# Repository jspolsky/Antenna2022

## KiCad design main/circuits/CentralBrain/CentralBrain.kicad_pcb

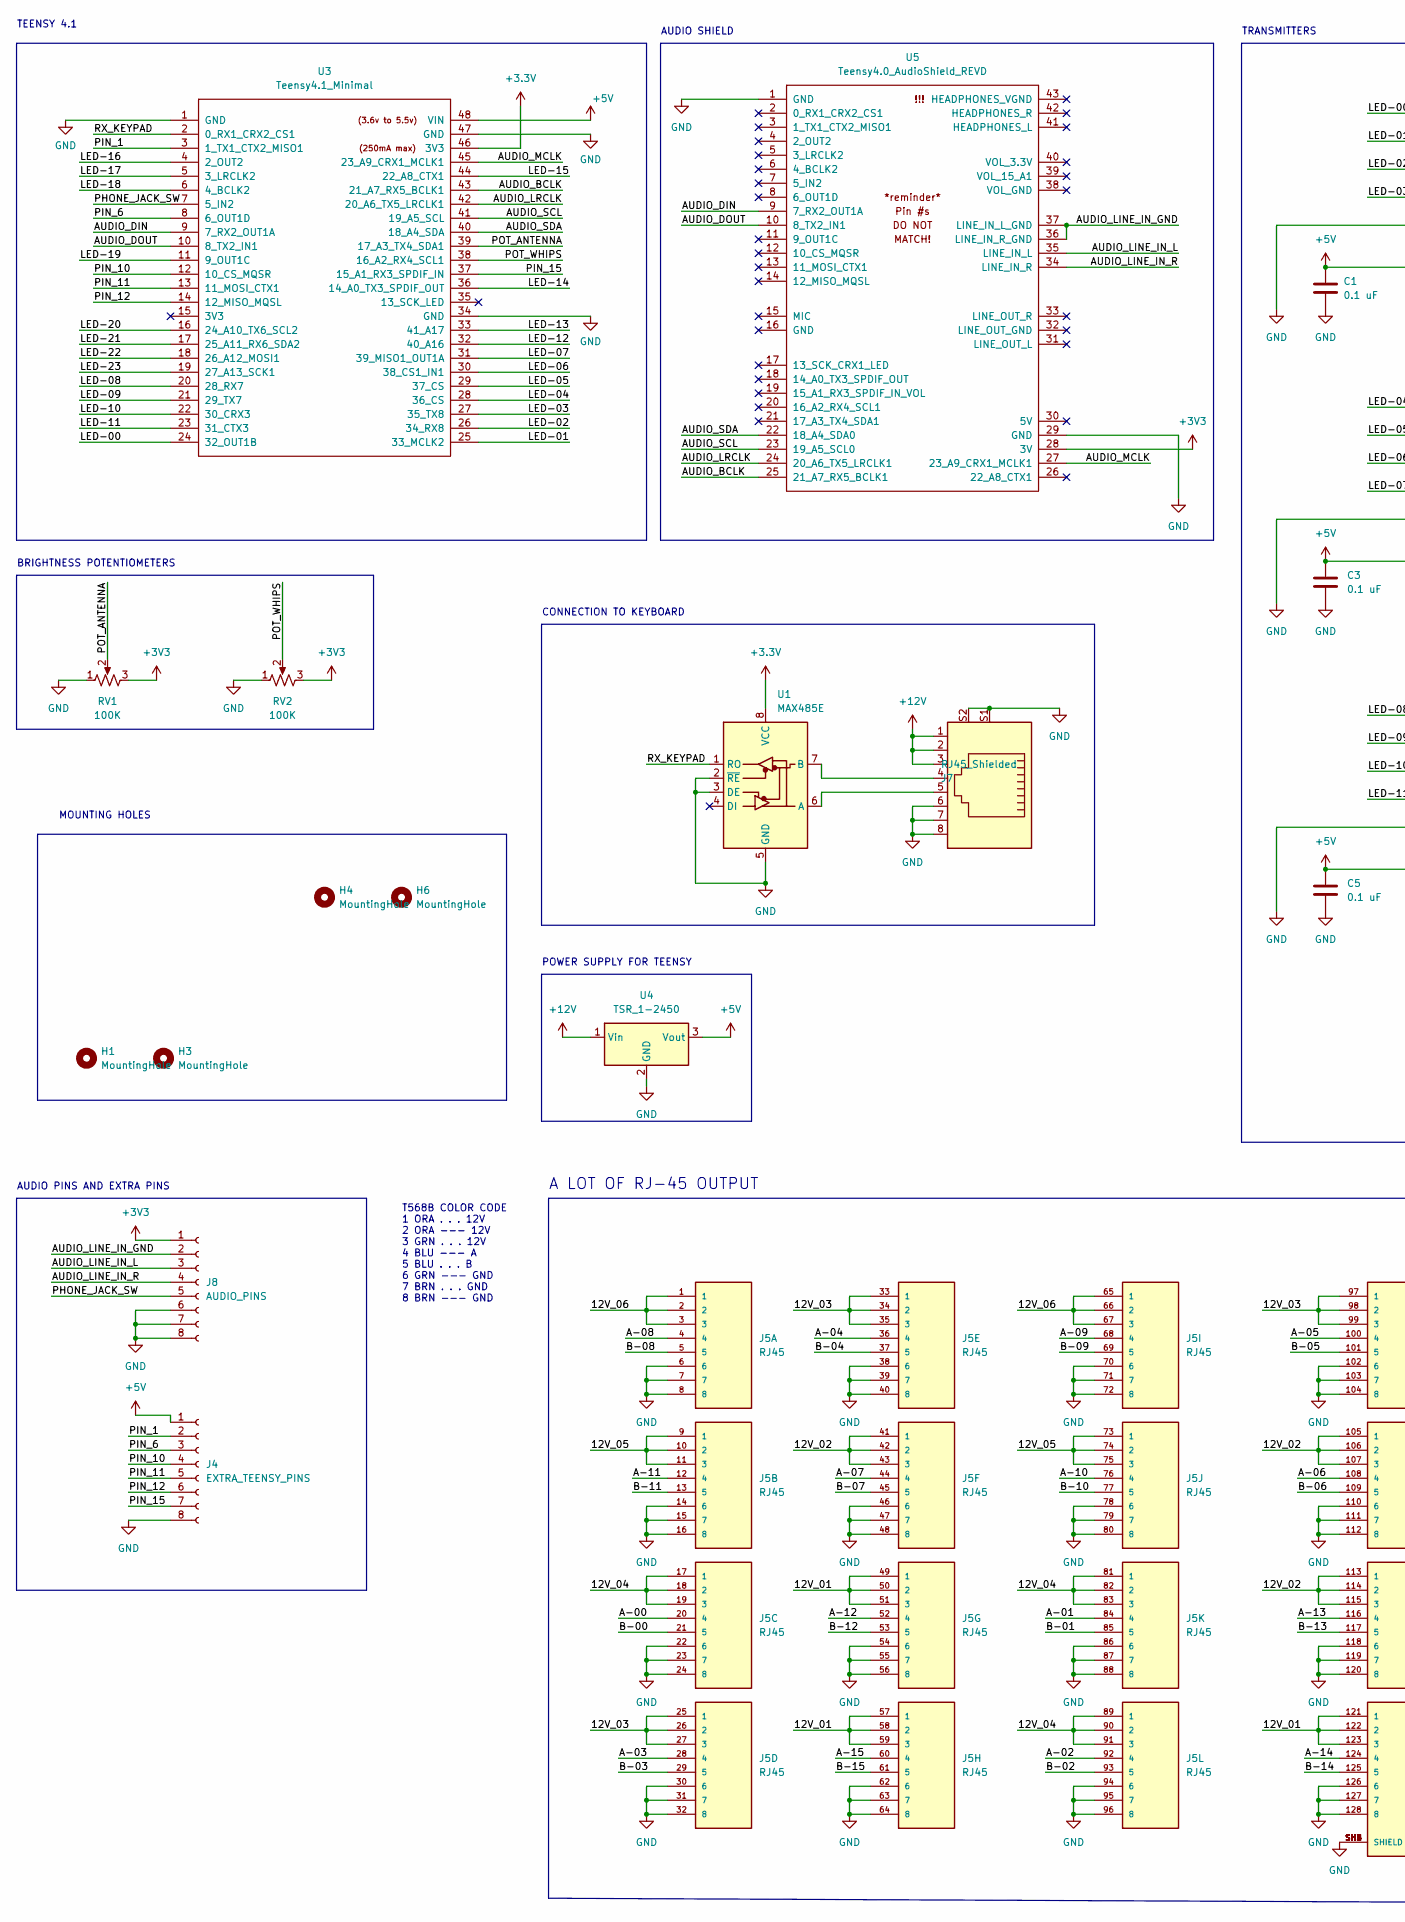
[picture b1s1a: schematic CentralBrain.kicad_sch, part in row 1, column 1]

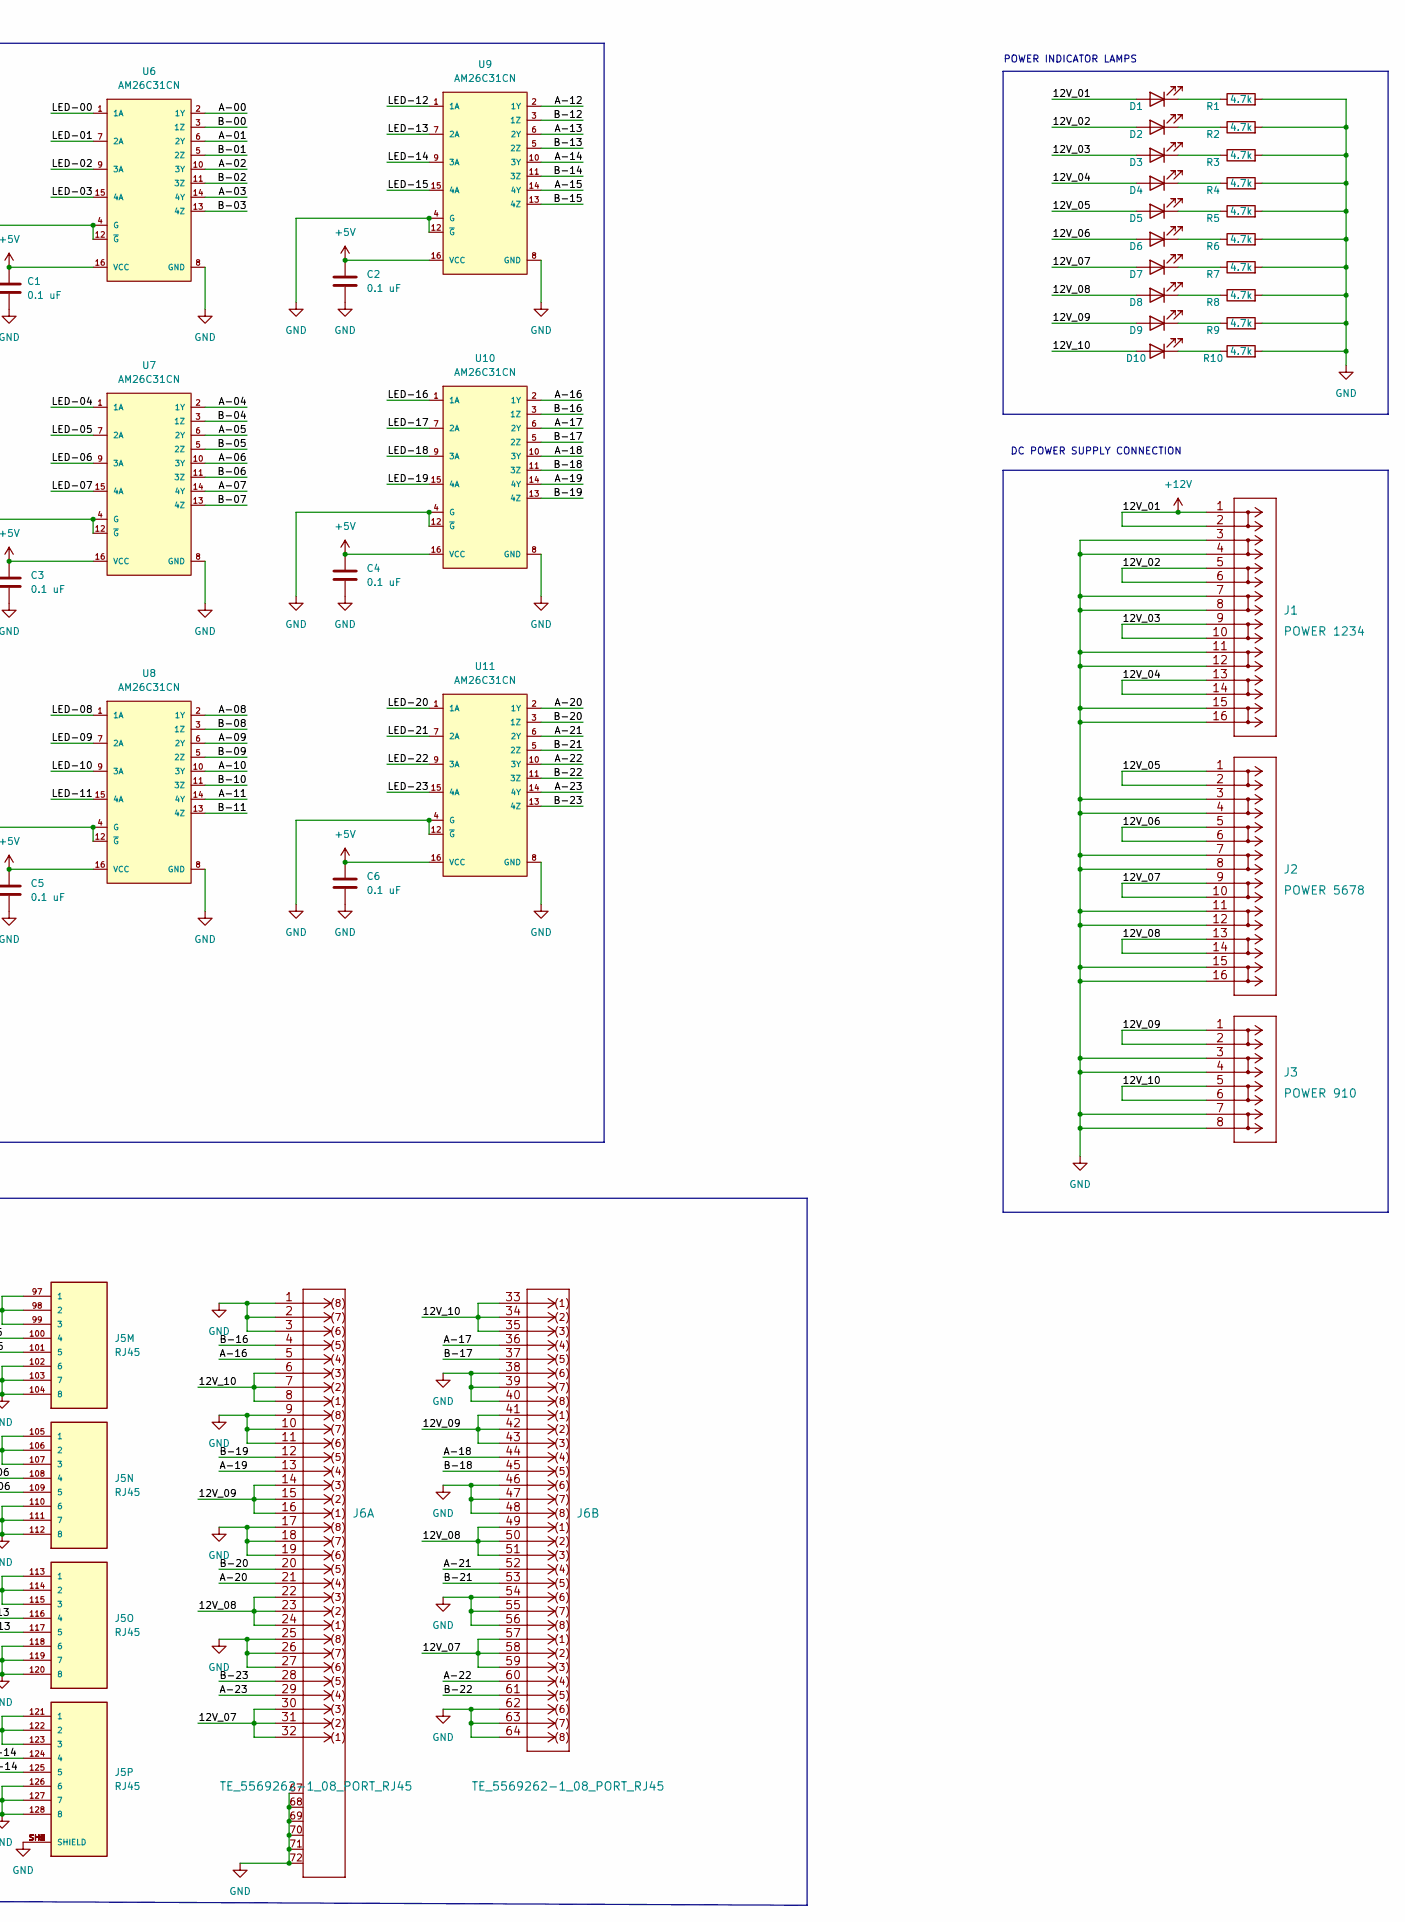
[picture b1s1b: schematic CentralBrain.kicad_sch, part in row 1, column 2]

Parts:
C1, C2, C3, C4, C5, C6: 0.1 uF; C_0805_2012Metric_Pad1.18x1.45mm_HandSolder
D1, D2, D3, D4, D5, D6, D7, D8, D9, D10: LED; LED_D3.0mm
H1, H3, H4, H6: MountingHole; MountingHole_3.5mm
J1: POWER 1234; WAGO-2604-1308
J2: POWER 5678; WAGO-2604-1308
J3: POWER 910; WAGO-2604-1304
J4: EXTRA_TEENSY_PINS; CUI_term_block_8_TB004-508-08BE
J5: RJ45; TE_5569264-1_16_Port_RJ45
J6: TE_5569262-1_08_PORT_RJ45; TE_5569262-1_08_Port_RJ45
J7: RJ45_Shielded; RJ45-ASSMANN_A-2004-1-4-LP-N-R
J8: AUDIO_PINS; CUI_term_block_8_TB004-508-08BE
R1, R2, R3, R4, R5, R6, R7, R8, R9, R10: 4.7k; R_Axial_DIN0207_L6.3mm_D2.5mm_P7.62mm_Horizontal
RV1, RV2: 100K; Potentiometer_Alpha_RD901F-40-00D_Single_Vertical
U1: MAX485E; Max485-Module
U3: Teensy4.1_Minimal; Teensy41_Minimal
U4: TSR_1-2450; Converter_DCDC_TRACO_TSR-1_THT
U5: Teensy4.0_AudioShield_REVD; Teensy4.0_Audioshield_RevD
U6, U7, U8, U9, U10, U11: AM26C31CN; Rating Catalog; Supply VoltagesV 5

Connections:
+5V: C1.1, C2.1, C3.1, C4.1, C5.1, C6.1, J4.1, U3.48 (VIN), U4.3 (Vout), U6.16 (VCC), U7.16 (VCC), U8.16 (VCC), U9.16 (VCC), U10.16 (VCC), U11.16 (VCC)
+12V: D1.2 (A), J1.1, J1.2, J5.49 (1), J5.50 (2), J5.51 (3), J5.57 (1), J5.58 (2), J5.59 (3), J5.121 (1), J5.122 (2), J5.123 (3), J7.1, J7.2, J7.3, U4.1 (Vin)
/12V_02: D2.2 (A), J1.5, J1.6, J5.41 (1), J5.42 (2), J5.43 (3), J5.105 (1), J5.106 (2), J5.107 (3), J5.113 (1), J5.114 (2), J5.115 (3)
/12V_03: D3.2 (A), J1.9, J1.10, J5.25 (1), J5.26 (2), J5.27 (3), J5.33 (1), J5.34 (2), J5.35 (3), J5.97 (1), J5.98 (2), J5.99 (3)
/12V_04: D4.2 (A), J1.13, J1.14, J5.17 (1), J5.18 (2), J5.19 (3), J5.81 (1), J5.82 (2), J5.83 (3), J5.89 (1), J5.90 (2), J5.91 (3)
/12V_05: D5.2 (A), J2.1, J2.2, J5.9 (1), J5.10 (2), J5.11 (3), J5.73 (1), J5.74 (2), J5.75 (3)
/12V_06: D6.2 (A), J2.5, J2.6, J5.1, J5.2, J5.3, J5.65 (1), J5.66 (2), J5.67 (3)
/12V_07: D7.2 (A), J2.9, J2.10, J6.30, J6.31, J6.32, J6.57, J6.58, J6.59
/12V_08: D8.2 (A), J2.13, J2.14, J6.22, J6.23, J6.24, J6.49, J6.50, J6.51
/12V_09: D9.2 (A), J3.1, J3.2, J6.14, J6.15, J6.16, J6.41, J6.42, J6.43
/12V_10: D10.2 (A), J3.5, J3.6, J6.6, J6.7, J6.8, J6.33, J6.34, J6.35
/A-00: J5.20 (4), U6.2 (1Y)
/A-01: J5.84 (4), U6.6 (2Y)
/A-02: J5.92 (4), U6.10 (3Y)
/A-03: J5.28 (4), U6.14 (4Y)
/A-04: J5.36 (4), U7.2 (1Y)
/A-05: J5.100 (4), U7.6 (2Y)
/A-06: J5.108 (4), U7.10 (3Y)
/A-07: J5.44 (4), U7.14 (4Y)
/A-08: J5.4, U8.2 (1Y)
/A-09: J5.68 (4), U8.6 (2Y)
/A-10: J5.76 (4), U8.10 (3Y)
/A-11: J5.12 (4), U8.14 (4Y)
/A-12: J5.52 (4), U9.2 (1Y)
/A-13: J5.116 (4), U9.6 (2Y)
/A-14: J5.124 (4), U9.10 (3Y)
/A-15: J5.60 (4), U9.14 (4Y)
/A-16: J6.5, U10.2 (1Y)
/A-17: J6.36, U10.6 (2Y)
/A-18: J6.44, U10.10 (3Y)
/A-19: J6.13, U10.14 (4Y)
/A-20: J6.21, U11.2 (1Y)
/A-21: J6.52, U11.6 (2Y)
/A-22: J6.60, U11.10 (3Y)
/A-23: J6.29, U11.14 (4Y)
/AUDIO_BCLK: U3.43 (21_A7_RX5_BCLK1), U5.25 (21_A7_RX5_BCLK1)
/AUDIO_DIN: U3.9 (7_RX2_OUT1A), U5.9 (7_RX2_OUT1A)
/AUDIO_DOUT: U3.10 (8_TX2_IN1), U5.10 (8_TX2_IN1)
/AUDIO_LINE_IN_GND: J8.2, U5.36 (LINE_IN_R_GND), U5.37 (LINE_IN_L_GND)
/AUDIO_LINE_IN_L: J8.3, U5.35 (LINE_IN_L)
/AUDIO_LINE_IN_R: J8.4, U5.34 (LINE_IN_R)
/AUDIO_LRCLK: U3.42 (20_A6_TX5_LRCLK1), U5.24 (20_A6_TX5_LRCLK1)
/AUDIO_MCLK: U3.45 (23_A9_CRX1_MCLK1), U5.27 (23_A9_CRX1_MCLK1)
/AUDIO_SCL: U3.41 (19_A5_SCL), U5.23 (19_A5_SCL0)
/AUDIO_SDA: U3.40 (18_A4_SDA), U5.22 (18_A4_SDA0)
/B-00: J5.21 (5), U6.3 (1Z)
/B-01: J5.85 (5), U6.5 (2Z)
/B-02: J5.93 (5), U6.11 (3Z)
/B-03: J5.29 (5), U6.13 (4Z)
/B-04: J5.37 (5), U7.3 (1Z)
/B-05: J5.101 (5), U7.5 (2Z)
/B-06: J5.109 (5), U7.11 (3Z)
/B-07: J5.45 (5), U7.13 (4Z)
/B-08: J5.5, U8.3 (1Z)
/B-09: J5.69 (5), U8.5 (2Z)
/B-10: J5.77 (5), U8.11 (3Z)
/B-11: J5.13 (5), U8.13 (4Z)
/B-12: J5.53 (5), U9.3 (1Z)
/B-13: J5.117 (5), U9.5 (2Z)
/B-14: J5.125 (5), U9.11 (3Z)
/B-15: J5.61 (5), U9.13 (4Z)
/B-16: J6.4, U10.3 (1Z)
/B-17: J6.37, U10.5 (2Z)
/B-18: J6.45, U10.11 (3Z)
/B-19: J6.12, U10.13 (4Z)
/B-20: J6.20, U11.3 (1Z)
/B-21: J6.53, U11.5 (2Z)
/B-22: J6.61, U11.11 (3Z)
/B-23: J6.28, U11.13 (4Z)
/LED-00: U3.24 (32_OUT1B), U6.1 (1A)
/LED-01: U3.25 (33_MCLK2), U6.7 (2A)
/LED-02: U3.26 (34_RX8), U6.9 (3A)
/LED-03: U3.27 (35_TX8), U6.15 (4A)
/LED-04: U3.28 (36_CS), U7.1 (1A)
/LED-05: U3.29 (37_CS), U7.7 (2A)
/LED-06: U3.30 (38_CS1_IN1), U7.9 (3A)
/LED-07: U3.31 (39_MISO1_OUT1A), U7.15 (4A)
/LED-08: U3.20 (28_RX7), U8.1 (1A)
/LED-09: U3.21 (29_TX7), U8.7 (2A)
/LED-10: U3.22 (30_CRX3), U8.9 (3A)
/LED-11: U3.23 (31_CTX3), U8.15 (4A)
/LED-12: U3.32 (40_A16), U9.1 (1A)
/LED-13: U3.33 (41_A17), U9.7 (2A)
/LED-14: U3.36 (14_A0_TX3_SPDIF_OUT), U9.9 (3A)
/LED-15: U3.44 (22_A8_CTX1), U9.15 (4A)
/LED-16: U3.4 (2_OUT2), U10.1 (1A)
/LED-17: U3.5 (3_LRCLK2), U10.7 (2A)
/LED-18: U3.6 (4_BCLK2), U10.9 (3A)
/LED-19: U3.11 (9_OUT1C), U10.15 (4A)
/LED-20: U3.16 (24_A10_TX6_SCL2), U11.1 (1A)
/LED-21: U3.17 (25_A11_RX6_SDA2), U11.7 (2A)
/LED-22: U3.18 (26_A12_MOSI1), U11.9 (3A)
/LED-23: U3.19 (27_A13_SCK1), U11.15 (4A)
/PHONE_JACK_SW: J8.5, U3.7 (5_IN2)
/PIN_1: J4.2, U3.3 (1_TX1_CTX2_MISO1)
/PIN_6: J4.3, U3.8 (6_OUT1D)
/PIN_10: J4.4, U3.12 (10_CS_MQSR)
/PIN_11: J4.5, U3.13 (11_MOSI_CTX1)
/PIN_12: J4.6, U3.14 (12_MISO_MQSL)
/PIN_15: J4.7, U3.37 (15_A1_RX3_SPDIF_IN)
/POT_ANTENNA: RV1.2, U3.39 (17_A3_TX4_SDA1)
/POT_WHIPS: RV2.2, U3.38 (16_A2_RX4_SCL1)
/RX_KEYPAD: U1.1 (RO), U3.2 (0_RX1_CRX2_CS1)
GND: C1.2, C2.2, C3.2, C4.2, C5.2, C6.2, J1.3, J1.4, J1.7, J1.8, J1.11, J1.12, J1.15, J1.16, J2.3, J2.4, J2.7, J2.8, J2.11, J2.12, J2.15, J2.16, J3.3, J3.4, J3.7, J3.8, J4.8, J5.6, J5.7, J5.8, J5.14 (6), J5.15 (7), J5.16 (8), J5.22 (6), J5.23 (7), J5.24 (8), J5.30 (6), J5.31 (7), J5.32 (8), J5.38 (6), J5.39 (7), J5.40 (8), J5.46 (6), J5.47 (7), J5.48 (8), J5.54 (6), J5.55 (7), J5.56 (8), J5.62 (6), J5.63 (7), J5.64 (8), J5.70 (6), J5.71 (7), J5.72 (8), J5.78 (6), J5.79 (7), J5.80 (8), J5.86 (6), J5.87 (7), J5.88 (8), J5.94 (6), J5.95 (7), J5.96 (8), J5.102 (6), J5.103 (7), J5.104 (8), J5.110 (6), J5.111 (7), J5.112 (8), J5.118 (6), J5.119 (7), J5.120 (8), J5.126 (6), J5.127 (7), J5.128 (8), J5.SH1 (SHIELD), J5.SH2 (SHIELD), J5.SH3 (SHIELD), J5.SH4 (SHIELD), J5.SH5 (SHIELD), J5.SH6 (SHIELD), J6.1, J6.2, J6.3, J6.9, J6.10, J6.11, J6.17, J6.18, J6.19, J6.25, J6.26, J6.27, J6.38, J6.39, J6.40, J6.46, J6.47, J6.48, J6.54, J6.55, J6.56, J6.62, J6.63, J6.64, J6.67 (SH67), J6.68 (SH68), J6.69 (SH69), J6.70 (SH70), J6.71 (SH71), J6.72 (SH72), J7.6, J7.7, J7.8, J7.S1, J7.S2, J8.6, J8.7, J8.8, R1.2, R2.2, R3.2, R4.2, R5.2, R6.2, R7.2, R8.2, R9.2, R10.2, RV1.1, RV2.1, U1.2 (~RE), U1.3 (DE), U1.5 (GND), U3.1 (GND), U3.34 (GND), U3.47 (GND), U4.2 (GND), U5.1 (GND), U5.29 (GND), U6.4 (G), U6.8 (GND), U6.12 (~G), U7.4 (G), U7.8 (GND), U7.12 (~G), U8.4 (G), U8.8 (GND), U8.12 (~G), U9.4 (G), U9.8 (GND), U9.12 (~G), U10.4 (G), U10.8 (GND), U10.12 (~G), U11.4 (G), U11.8 (GND), U11.12 (~G)
unnamed: D1.1 (K), R1.1
unnamed: D2.1 (K), R2.1
unnamed: D3.1 (K), R3.1
unnamed: D4.1 (K), R4.1
unnamed: D5.1 (K), R5.1
unnamed: D6.1 (K), R6.1
unnamed: D7.1 (K), R7.1
unnamed: D8.1 (K), R8.1
unnamed: D9.1 (K), R9.1
unnamed: D10.1 (K), R10.1
unnamed: J7.4, U1.7 (B)
unnamed: J7.5, U1.6 (A)

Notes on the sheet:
MOUNTING HOLES
TRANSMITTERS
POWER INDICATOR LAMPS
T568B COLOR CODE 1 ORA . . . 12V 2 ORA --- 12V 3 GRN . . . 12V 4 BLU --- A 5 BLU . . . B 6 GRN --- GND 7 BRN . . . GND 8 BRN --- GND
CONNECTION TO KEYBOARD
POWER SUPPLY FOR TEENSY
A LOT OF RJ-45 OUTPUT
AUDIO PINS AND EXTRA PINS
TEENSY 4.1
DC POWER SUPPLY CONNECTION
BRIGHTNESS POTENTIOMETERS
AUDIO SHIELD

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
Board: 4 copper layers, 50 parts (0 on the bottom side), 117 nets, no tracks yet.

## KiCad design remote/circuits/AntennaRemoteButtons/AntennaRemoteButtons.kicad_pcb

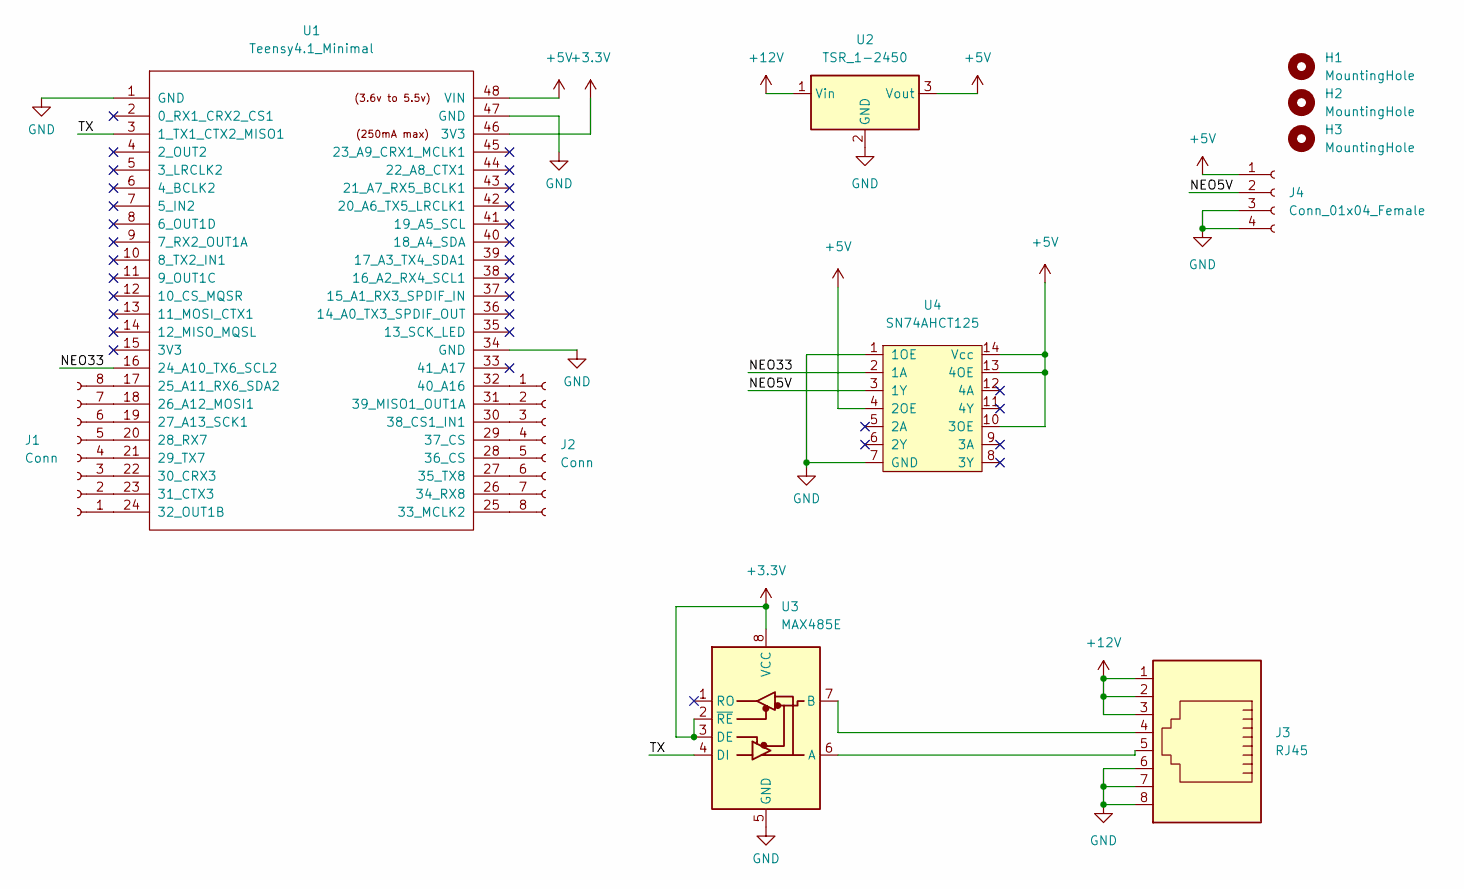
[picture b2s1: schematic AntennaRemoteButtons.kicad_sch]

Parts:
H1, H2, H3: MountingHole; MountingHole_5mm
J1, J2: Conn; CUI_term_block_8_TB004-508-08BE
J3: RJ45; RJ45-ASSMANN_A-2004-1-4-LP-N-R
J4: Conn_01x04_Female; CUI_term_block_4_CUI_TB004-508-04BE
U1: Teensy4.1_Minimal; Teensy41_Minimal
U2: TSR_1-2450; Converter_DCDC_TRACO_TSR-1_THT
U3: MAX485E; Max485-Module
U4: SN74AHCT125; SN74AHCT125N

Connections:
+3V3: U1.46 (3V3), U3.2 (~RE), U3.3 (DE), U3.8 (VCC)
+5V: J4.1, U1.48 (VIN), U2.3 (Vout), U4.4 (2OE), U4.10 (3OE), U4.13 (4OE), U4.14 (Vcc)
+12V: J3.1, J3.2, J3.3, U2.1 (Vin)
/NEO5V: J4.2, U4.3 (1Y)
/NEO33: U1.16 (24_A10_TX6_SCL2), U4.2 (1A)
/TX: U1.3 (1_TX1_CTX2_MISO1), U3.4 (DI)
GND: J3.6, J3.7, J3.8, J4.3, J4.4, U1.1 (GND), U1.34 (GND), U1.47 (GND), U2.2 (GND), U3.5 (GND), U4.1 (1OE), U4.7 (GND)
unnamed: J1.1, U1.24 (32_OUT1B)
unnamed: J1.2, U1.23 (31_CTX3)
unnamed: J1.3, U1.22 (30_CRX3)
unnamed: J1.4, U1.21 (29_TX7)
unnamed: J1.5, U1.20 (28_RX7)
unnamed: J1.6, U1.19 (27_A13_SCK1)
unnamed: J1.7, U1.18 (26_A12_MOSI1)
unnamed: J1.8, U1.17 (25_A11_RX6_SDA2)
unnamed: J2.1, U1.32 (40_A16)
unnamed: J2.2, U1.31 (39_MISO1_OUT1A)
unnamed: J2.3, U1.30 (38_CS1_IN1)
unnamed: J2.4, U1.29 (37_CS)
unnamed: J2.5, U1.28 (36_CS)
unnamed: J2.6, U1.27 (35_TX8)
unnamed: J2.7, U1.26 (34_RX8)
unnamed: J2.8, U1.25 (33_MCLK2)
unnamed: J3.4, U3.7 (B)
unnamed: J3.5, U3.6 (A)

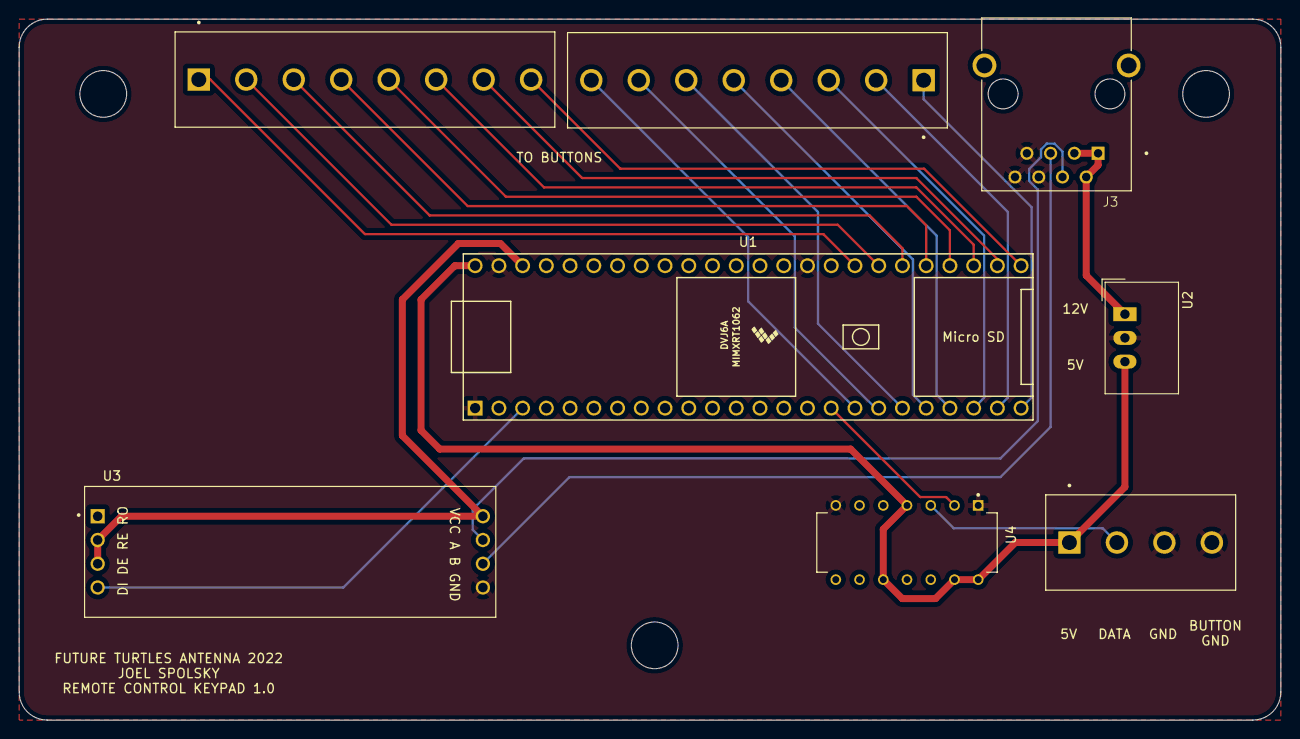
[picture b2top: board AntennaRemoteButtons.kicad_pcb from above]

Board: 2 copper layers, 135.0 x 75.0 mm, 11 parts (0 on the bottom side), 25 nets.

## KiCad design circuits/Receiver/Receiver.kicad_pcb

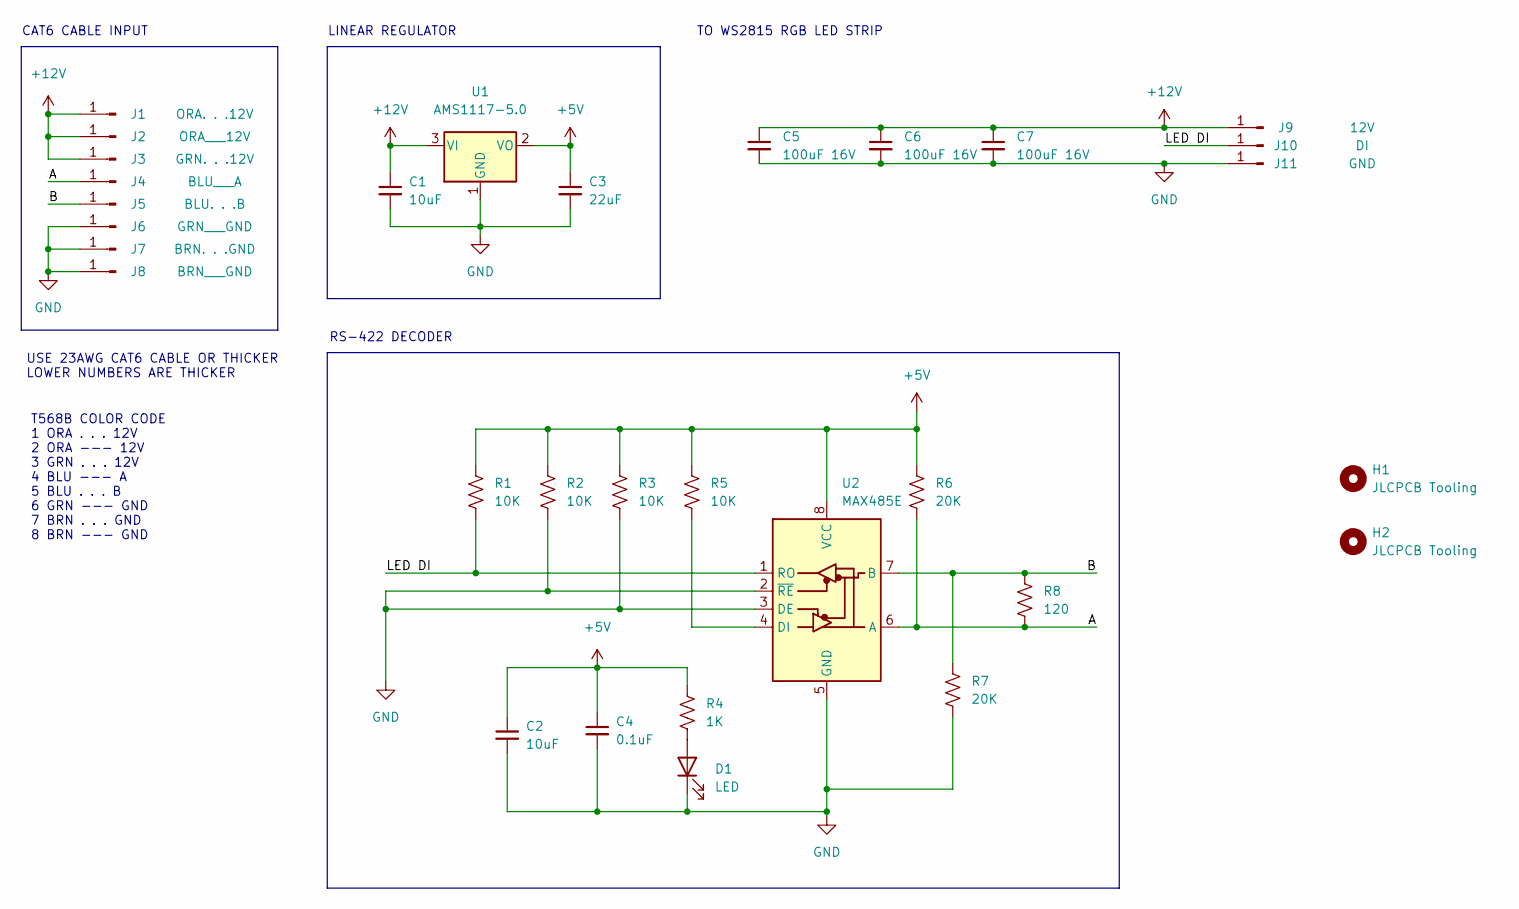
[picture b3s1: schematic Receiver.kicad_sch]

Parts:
C1, C2: 10uF; C_0805_2012Metric; JLCPCB C15850
C3: 22uF; C_0805_2012Metric; JLCPCB C45783
C4: 0.1uF; C_0402_1005Metric; JLCPCB C1525
C5, C6, C7: 100uF 16V; C_1210_3225Metric; JLCPCB C90143
D1: LED; LED_0805_2012Metric; JLCPCB C84256
H1, H2: JLCPCB Tooling; JCLPCB_Tooling_Hole
J1: ORA. . .12V; SolderWire-0.25sqmm_1x01_D0.65mm_OD1.7mm
J2: ORA___12V; SolderWire-0.25sqmm_1x01_D0.65mm_OD1.7mm
J3: GRN. . .12V; SolderWire-0.25sqmm_1x01_D0.65mm_OD1.7mm
J4: BLU___A; SolderWire-0.25sqmm_1x01_D0.65mm_OD1.7mm
J5: BLU. . .B; SolderWire-0.25sqmm_1x01_D0.65mm_OD1.7mm
J6: GRN___GND; SolderWire-0.25sqmm_1x01_D0.65mm_OD1.7mm
J7: BRN. . .GND; SolderWire-0.25sqmm_1x01_D0.65mm_OD1.7mm
J8: BRN___GND; SolderWire-0.25sqmm_1x01_D0.65mm_OD1.7mm
J9: 12V; SolderWire-1sqmm_1x01_D1.4mm_OD2.7mm
J10: DI; SolderWire-1sqmm_1x01_D1.4mm_OD2.7mm
J11: GND; SolderWire-1sqmm_1x01_D1.4mm_OD2.7mm
R1, R2, R3, R5: 10K; R_0603_1608Metric; JLCPCB C25804
R4: 1K; R_0603_1608Metric; JLCPCB C21190
R6, R7: 20K; R_0603_1608Metric; JLCPCB C4184
R8: 120; R_0603_1608Metric; JLCPCB C22787
U1: AMS1117-5.0; SOT-223-3_TabPin2; JLCPCB C6187
U2: MAX485E; SOIC-8_3.9x4.9mm_P1.27mm; JLCPCB C19738

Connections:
+5V: C2.1, C3.1, C4.1, R1.1, R2.1, R3.1, R4.1, R5.1, R6.1, U1.2 (VO), U2.8 (VCC)
+12V: C1.1, C5.1, C6.1, C7.1, J1.1, J2.1, J3.1, J9.1, U1.3 (VI)
/A: J4.1, R6.2, R8.2, U2.6 (A)
/B: J5.1, R7.1, R8.1, U2.7 (B)
/LED DI: J10.1, R1.2, U2.1 (RO)
GND: C1.2, C2.2, C3.2, C4.2, C5.2, C6.2, C7.2, D1.1 (K), J6.1, J7.1, J8.1, J11.1, R2.2, R3.2, R7.2, U1.1 (GND), U2.2 (~RE), U2.3 (DE), U2.5 (GND)
unnamed: D1.2 (A), R4.2
unnamed: R5.2, U2.4 (DI)

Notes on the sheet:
TO WS2815 RGB LED STRIP
CAT6 CABLE INPUT
LINEAR REGULATOR
T568B COLOR CODE 1 ORA . . . 12V 2 ORA --- 12V 3 GRN . . . 12V 4 BLU --- A 5 BLU . . . B 6 GRN --- GND 7 BRN . . . GND 8 BRN --- GND
RS-422 DECODER
USE 23AWG CAT6 CABLE OR THICKER LOWER NUMBERS ARE THICKER

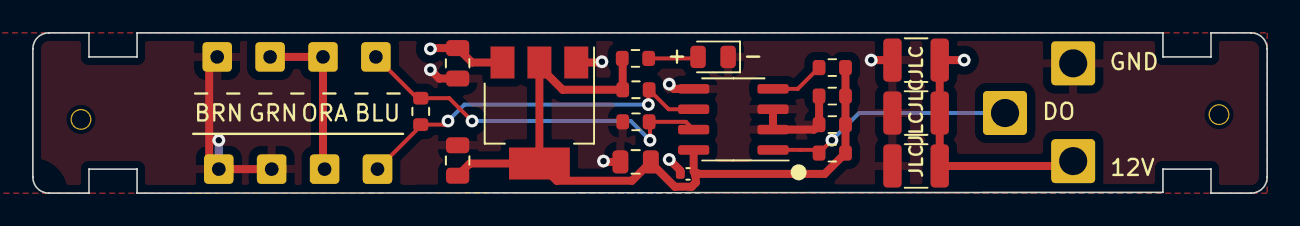
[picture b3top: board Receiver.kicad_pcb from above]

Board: 4 copper layers, 77.0 x 10.0 mm, 31 parts (0 on the bottom side), 8 nets.

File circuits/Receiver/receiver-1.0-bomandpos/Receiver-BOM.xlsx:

Receiver-BOM
Comment | Designator | Footprint | Description | JLCPCB Part #
10uF | C1 C2 | 0805 | Unpolarized capacitor, small symbol | C15850
22uF | C3 | 0805 | Unpolarized capacitor, small symbol | C45783
0.1uF | C4 | 0402 | Unpolarized capacitor, small symbol | C1525
100uF 16V | C5 C6 C7 | 1210 | Unpolarized capacitor, small symbol | C90143
LED | D1 | 0805 | Light emitting diode | C84256
10K | R1 R2 R3 R5 | 0603 | Resistor, US symbol | C25804
1K | R4 | 0603 | Resistor, US symbol | C21190
20K | R6 R7 | 0603 | Resistor, US symbol | C4184
120 | R8 | 0603 | Resistor, US symbol | C22787
AMS1117-5.0 | U1 | SOT-223 | 1A Low Dropout regulator, positive, 5.0V fixed output, SOT-223 | C6187
MAX485E | U2 | SOIC-8 | Half duplex RS-485/RS-422, 2.5 Mbps, ±15kV electro-static discharge (ESD) prote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 | C19738

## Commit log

2022-05-06 Code for the Future Turtles antenna 2022
2022-05-07 first design of receiver PCB
2022-05-08 Use zipties for strain relief on cables
2022-05-08 1.0 sent to production
2022-05-08 stuff
2022-05-19 my ol fren dbgprintf
2022-05-19 don't commit kicad backups
2022-05-19 a little test code to make sure port expander is working
2022-05-21 Moved into a subdirectory
2022-05-21 moved things into main
2022-05-21 gitignoring
2022-05-21 Adding remote control box as subdirectory
2022-05-21 arg .DS_Store die
2022-05-21 Incorporate FastLED
2022-05-21 fix rgb order
2022-05-23 Restructured code; use FastLED
2022-05-23 minor
2022-05-23 no need for level shifters! thanks chuck!
2022-06-02 started work on the central PCB
2022-06-02 lots of work on pcb
2022-06-03 Mechanical design of PCB mostly done
2022-06-03 ignore
2022-06-03 version 1.0 of board sent to mfr
2022-07-13 frickin .ds_store
2022-07-13 baseline. I'm about to start coding in earnest lol
2022-07-13 factor out brightness knobs
2022-07-13 brightness bracketing
2022-07-13 simplest possible utility functions for leds
2022-07-14 Picked 8 nice solid colors. Patterns NYI
2022-07-14 oops accidentally broke output
2022-07-14 added templates useful for creating new modules
2022-07-14 very rudimentary push button colors imma take a nap now
2022-07-22 solid color button interactivity done
2022-07-22 blinky red dot at the top; always max brightness
2022-07-22 carnival Whoosh! with physics
2022-07-28 reasonable first approximation of monochromeBasic
2022-07-28 first half of eljibbity
2022-07-29 lgbtq is beautiful
2022-07-29 sea and renegade
2022-07-29 brown? ugh
2022-07-29 ufo pattern
2022-07-29 ufo tweek
2022-07-29 fire and stars
2022-07-29 more stars!
2022-07-29 trans flag variant
2022-07-29 smoother whoosh in from the sides
2022-07-29 faster cycle
2022-07-29 finished all the buttons!
2022-07-29 eliminated obsolete test code
2022-07-29 respond to audio jack being in/out
2022-07-29 vu meter audio visualization
2022-07-29 calm
2022-07-29 nicer audio reactive mode
2022-08-01 antenna will be to the left of the whips
2022-08-01 slightly cooler stars with blue things
2022-08-01 switch back to the main show if audio stops
2022-08-01 reasonable antenna option for music.
2022-08-02 don't need to use output of audio shield
2022-08-02 enough of FFT is working to make me happy
2022-08-02 minor cleanup
2022-08-02 nice FFT display. DONE!
2022-08-02 cool squishing effect at top
2022-08-02 more firey fire
2022-08-03 improved whips in (renegade/sea) modes
2022-08-03 improved stars? I think?

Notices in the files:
parts and their libraries:
Copyright 2021 Accelerated Designs. All rights reserved.
